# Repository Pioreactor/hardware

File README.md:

### HAT hardware setup

#### Installation

0. Install git: `sudo apt-get install git -y`
1. git clone this repo to your Raspberry Pi: `git clone --recurse-submodules https://github.com/Pioreactor/hardware.git && cd hardware`
2. Install eeprom utils: `cd hats/eepromutils && make && sudo make install && cd ..`
3. Move some files over: `mv ../eeprom/write_eeprom.py eepromutils/ && mv ../eeprom/pioreactor_eeprom_settings.txt.template eepromutils/`

#### Setting up a new HAT

0. Attach the HAT to the RPi.
1. Run `sudo bash setup_HAT.py`
2. Record the serial number/UUID
2. After a `sudo reboot`, try  `pio version -v` to confirm that HATs version.

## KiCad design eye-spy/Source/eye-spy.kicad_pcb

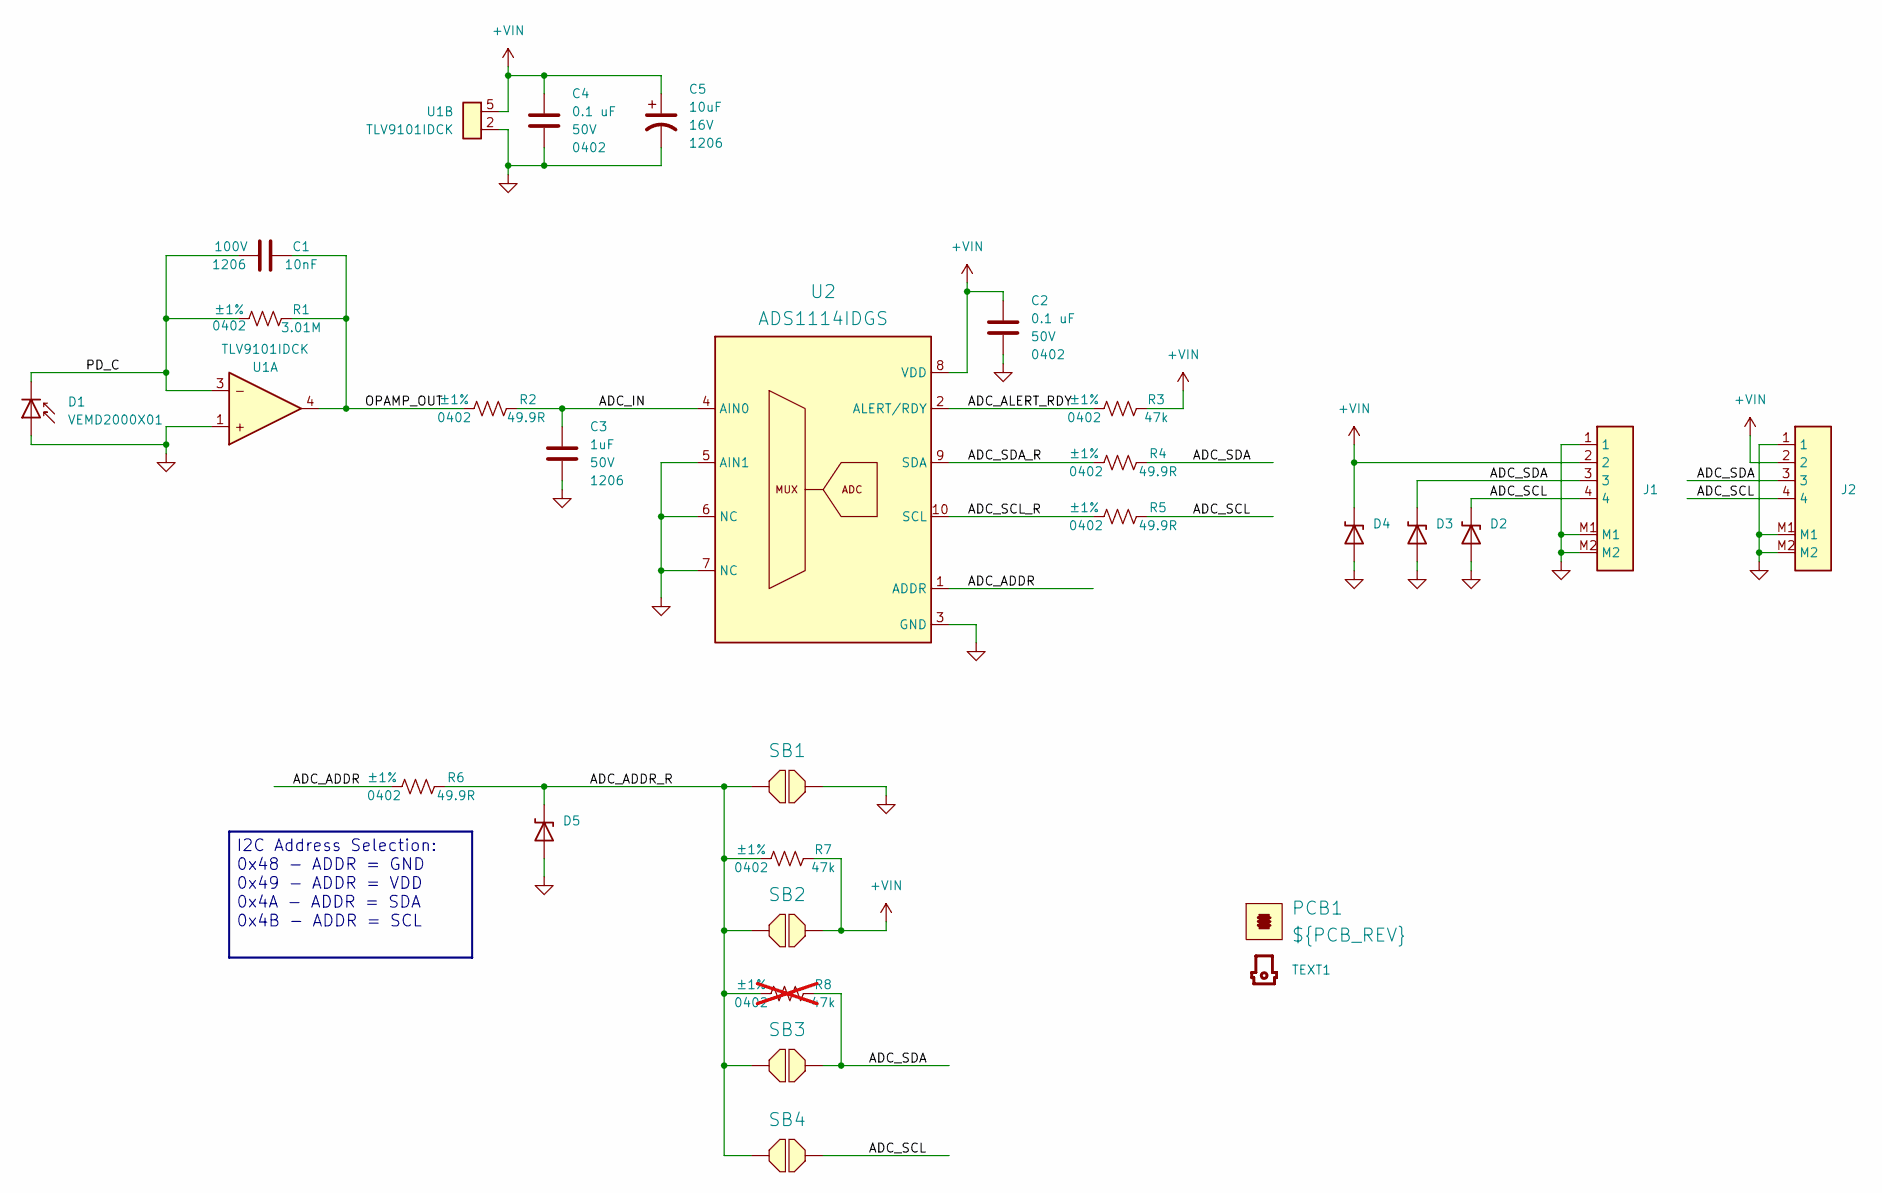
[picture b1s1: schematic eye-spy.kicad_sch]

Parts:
C1: 10nF; CAPC320X160X180L55N; Tolerance ±5%; Voltage 100V; Manufacturer Part Numbe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 GCM3195C2A103JA16D
C2, C4: 0.1 uF; CAPC100X50X55L25N; Tolerance ±10%; Voltage 50V; Manufacturer Part Numbe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 GRM155R71H104KE14J
C3: 1uF; CAPC320X160X180L55N; Tolerance ±10%; Voltage 50V; Manufacturer Part Numbe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 GRM31CR71H105KA61L
C5: 10uF; CAPPM320X160X180L85X120N; Tolerance ±10%; Voltage 16V; Manufacturer Part Numbe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 TAJA106K016RNJ
D1: VEMD2000X01; VITEC_VEMD2000X01; Manufacturer Part Numbe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 VEMD2000X01
D2, D3, D4, D5: DF2S6.8MFS,L3M; SODFL100X60X45L17X30N; Manufacturer Part Numbe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 DF2S6.8MFS,L3M
J1, J2: BM04B-SRSS-TB; JST_BM04B-SRSS-TB; Manufacturer Part Numbe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 BM04B-SRSS-TB
PCB1: ${PCB_REV}
R1: 3.01M; RESC100X50X40L25N; Tolerance ±1%; Manufacturer Part Numbe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 RC0402FR-073M01L
R2, R4, R5, R6: 49.9R; RESC100X50X40L25N; Tolerance ±1%; Manufacturer Part Numbe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 RC0402FR-0749R9L
R3, R7: 47k; RESC100X50X40L25N; Tolerance ±1%; Manufacturer Part Numbe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 RC0402FR-0747KL
R8: 47k; RESC100X50X40L25N; Tolerance ±1%; Manufacturer Part Numbe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 RC0402FR-0747KL; not fitted
SB1, SB2, SB3, SB4: R_0402_SB
TEXT1: logo
U1: TLV9101IDCK; SOP6-5P65_200X210X100L36X24N; Manufacturer Part Numbe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 TLV9101IDCK
U2: ADS1114IDGS; SOP10P50_300X490X110L55X22N; Manufacturer Part Numbe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 ADS1114IDGSR

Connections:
+VIN: C2.1, C4.1, C5.1, D4.1 (CATHODE), J1.2, J2.2, R3.2, R7.2, SB2.2, U1.5 (V+), U2.8 (VDD)
/ADC_ADDR: R6.1, U2.1 (ADDR)
/ADC_ADDR_R: D5.1 (CATHODE), R6.2, R7.1, R8.1, SB1.1, SB2.1, SB3.1, SB4.1
/ADC_ALERT_RDY: R3.1, U2.2 (ALERT/RDY)
/ADC_IN: C3.1, R2.2, U2.4 (AIN0)
/ADC_SCL: D2.1 (CATHODE), J1.4, J2.4, R5.2, SB4.2
/ADC_SCL_R: R5.1, U2.10 (SCL)
/ADC_SDA: D3.1 (CATHODE), J1.3, J2.3, R4.2, R8.2, SB3.2
/ADC_SDA_R: R4.1, U2.9 (SDA)
/OPAMP_OUT: C1.2, R1.2, R2.1, U1.4 (OUT)
/PD_C: C1.1, D1.1 (CATHODE), R1.1, U1.3 (IN-)
GND: C2.2, C3.2, C4.2, C5.2, D1.2 (ANODE), D2.2 (ANODE), D3.2 (ANODE), D4.2 (ANODE), D5.2 (ANODE), J1.1, J1.M1, J1.M2, J2.1, J2.M1, J2.M2, SB1.2, U1.1 (IN+), U1.2 (V-), U2.3 (GND), U2.5 (AIN1), U2.6 (NC), U2.7 (NC)

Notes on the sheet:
I2C Address Selection: 0x48 - ADDR = GND 0x49 - ADDR = VDD 0x4A - ADDR = SDA 0x4B - ADDR = SCL

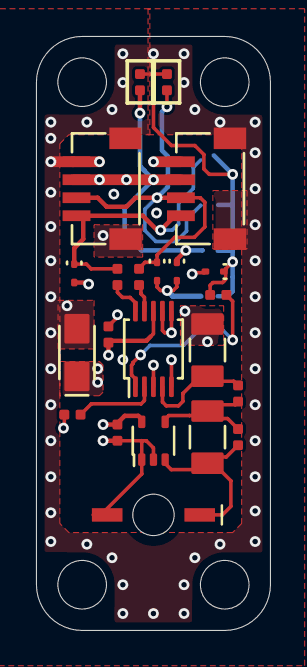
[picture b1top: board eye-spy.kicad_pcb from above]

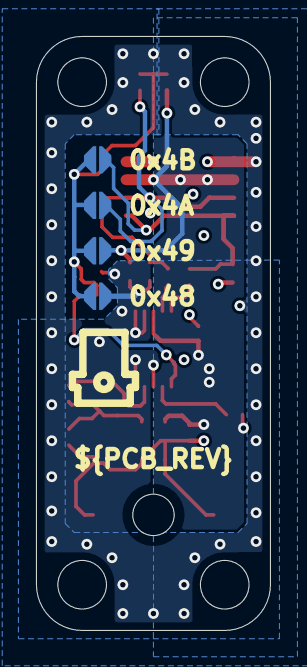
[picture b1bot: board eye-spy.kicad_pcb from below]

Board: 4 copper layers, 13.0 x 33.0 mm, 27 parts (5 on the bottom side), 12 nets.

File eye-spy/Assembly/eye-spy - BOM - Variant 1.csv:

"Reference","Qty","Description","Value","Manufacturer 1","Manufacturer Part Number 1"
"C1","1","CAP CER 10000PF 100V C0G 1206","10nF","Murata Electronics","GCM3195C2A103JA16D"
"C2,C4","2","CAP CER 0.1UF 50V X7R 0402","0.1 uF","Murata Electronics","GRM155R71H104KE14J"
"C3","1","CAP CER 1UF 50V X7R 1206","1uF","Murata Electronics","GRM31CR71H105KA61L"
"C5","1","CAP TANT 10UF 10% 16V 1206","10uF","KYOCERA AVX","TAJA106K016RNJ"
"D1","1","SENSOR PHOTODIODE 940NM 2SMD","VEMD2000X01","Vishay Semiconductor","VEMD2000X01"
"D2,D3,D4,D5","4","TVS DIODE 5V 15V SOD923","DF2S6.8MFS,L3M","Toshiba","DF2S6.8MFS,L3M"
"J1,J2","2","CONN HEADER SMD 4POS 1MM","BM04B-SRSS-TB","JST Sales America Inc.","BM04B-SRSS-TB"
"PCB1","1","PCB","3_20250920","",""
"R1","1","RES 3.01M OHM 1% 1/16W 0402","3.01M","Yageo","RC0402FR-073M01L"
"R2,R4,R5,R6","4","RES SMD 49.9 OHM 1% 1/16W 0402","49.9R","Yageo","RC0402FR-0749R9L"
"R3,R7","2","RES 47K OHM 1% 1/16W 0402","47k","Yageo","RC0402FR-0747KL"
"U1","1","IC OPAMP GP 1 CIRCUIT SC70-5","TLV9101IDCK","Texas Instruments","TLV9101IDCK"
"U2","1","IC ADC 16BIT SIGMA-DELTA 10VSSOP","ADS1114IDGS","Texas Instruments","ADS1114IDGSR"

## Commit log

2020-12-12 adding 3d files
2020-12-13 new holder with 8 angles
2020-12-14 shorter base
2021-12-14 adding eeprom file
2021-12-15 replace with template
2021-12-16 adding script to write our custom eeprom
2022-02-28 update here
2022-03-30 add more to eeprom
2022-08-22 small updates
2022-08-22 remove these; not using them anymore
2022-12-03 adding tests
2022-12-03 updates to write eeprom
2022-12-03 readme
2022-12-04 more
2022-12-04 adding hats repo as submodule
2022-12-04 top level readme
2023-02-16 fixes
2023-11-02 turn off leds after test
2023-11-21 update some testS
2023-11-23 testes
2024-01-09 adding heater for 20ml pioreactor
2024-04-27 Create LICENSE
2024-04-27 Update LICENSE
2024-07-29 adding assembly docs
2024-08-26 STEP files of hardware
2026-01-16 open source the temp hat
2026-01-16 cables
2026-04-15 step for eye-spy

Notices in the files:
parts and their libraries:
CopyrightYear: 2025
